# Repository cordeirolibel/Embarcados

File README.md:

# Sistemas Embarcados

- Modelagem, projeto e implementação. 
- Programação concorrente. 
- Núcleos operacionais. 
- Escalonamento.

 ----

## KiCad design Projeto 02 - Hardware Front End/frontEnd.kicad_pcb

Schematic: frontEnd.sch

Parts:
C1, C2: 220u; CP_Radial_D10.0mm_P7.50mm
C3: 68u; C_Rect_L29.0mm_W11.9mm_P27.50mm_MKT
C4, C5: 220n; C_Rect_L7.0mm_W2.5mm_P5.00mm
C6: 100n; C_Rect_L7.0mm_W2.5mm_P5.00mm
C7: 22n; C_Rect_L7.0mm_W2.5mm_P5.00mm
D1, D2, D3, D4: D; D_DO-35_SOD27_P5.08mm_Vertical_KathodeUp
J1: Power_Supply; PinSocket_1x03_P2.54mm_Vertical
J2: Signal_Input; PinSocket_1x02_P2.54mm_Vertical
J3: MCU_Interface; PinSocket_1x03_P2.54mm_Vertical
R1: 1k; R_Axial_DIN0207_L6.3mm_D2.5mm_P10.16mm_Horizontal
R2: 68k; R_Axial_DIN0207_L6.3mm_D2.5mm_P10.16mm_Horizontal
R4: 1M; R_Axial_DIN0207_L6.3mm_D2.5mm_P10.16mm_Horizontal
R5: 68; R_Axial_DIN0207_L6.3mm_D2.5mm_P10.16mm_Horizontal
U1: L78L12_TO92; TO-92_Inline
U2: L79L12_TO92; TO-92_Inline
U3: LM311; DIP-8_W7.62mm

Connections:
+12V: C4.1, C6.1, C7.1, D1.1, D3.2, U1.1 (VO), U3.8
-12V: C5.2, C6.2, C7.2, D2.2, D4.2, U2.3 (VO), U3.4
GND: C1.2, C2.1, C4.2, C5.1, J1.2, J2.2, R4.1, U1.2 (GND), U2.1 (GND), U3.3
unnamed: C1.1, D3.1, J1.1, U1.3 (VI)
unnamed: C2.2, D4.1, J1.3, U2.2 (VI)
unnamed: C3.1, R1.1
unnamed: C3.2, J2.1
unnamed: D1.2, D2.1, R1.2, R2.1
unnamed: J3.1, U3.1
unnamed: J3.2, R5.1, U3.7
unnamed: J3.3, R5.2
unnamed: R2.2, R4.2, U3.2

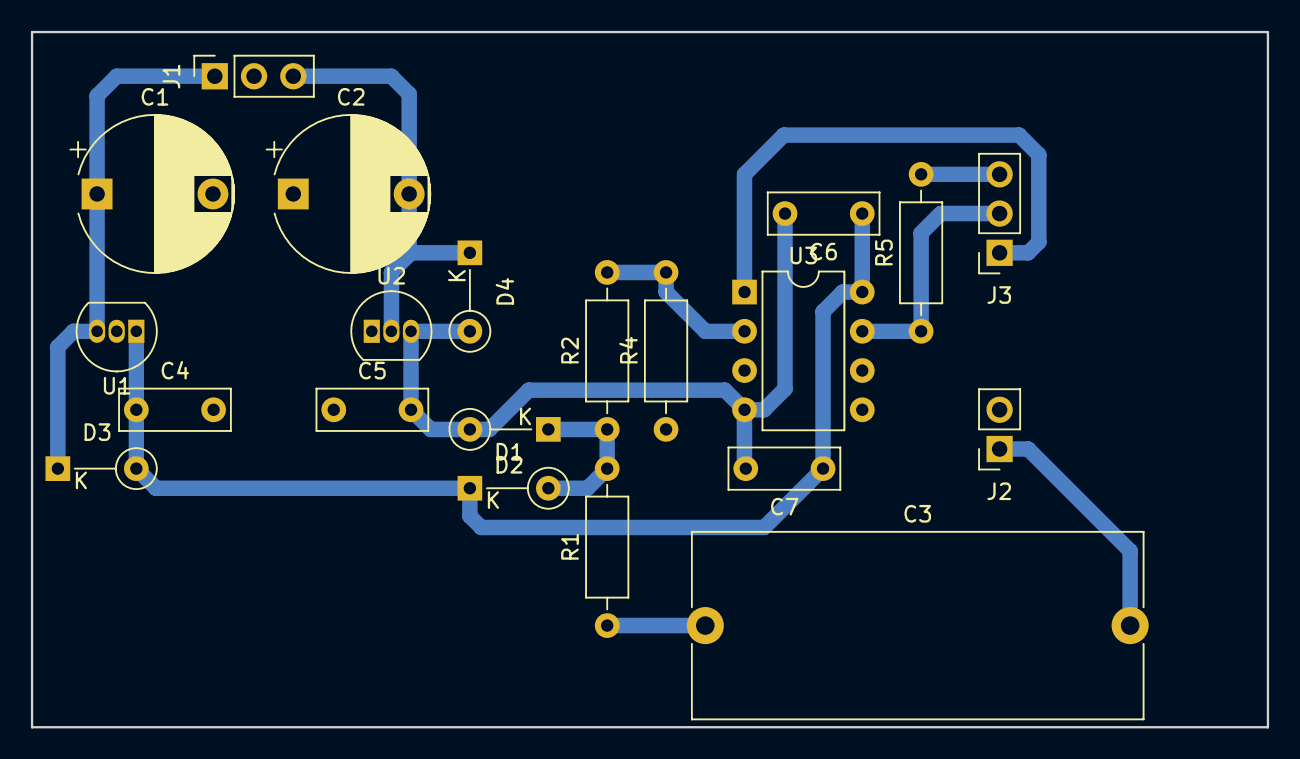
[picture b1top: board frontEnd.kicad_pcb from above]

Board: 2 copper layers, 80.0 x 45.0 mm, 21 parts (0 on the bottom side), 12 nets.

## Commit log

2018-09-27 Envio arquivos projeto 1
2018-10-03 add files
2018-10-05 add files lab02
2018-10-05 fix .h
2018-10-05 Correção da implementação do Device Driver do Contador
2018-10-12 Projeto da interface analógica
2018-10-13 Display + SysTick
2018-10-20 Projeto CCS quase 100%
2018-10-25 simple db
2018-10-26 projeto CCS final
2018-10-26 anonimação da displayLib + remoção dos inuteis
